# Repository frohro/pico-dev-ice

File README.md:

# <span style="text-transform: none;">The Pico Dev-iCE 📡</span>
**DSP Educational Vehicle & iCE40 Mixed-Signal Laboratory**

## 📌 Overview
The **Pico Dev-iCE** is a low-cost, high-performance "Lab-in-a-Box." It combines the high-speed programmable logic of a **Lattice iCE40UP5K FPGA** with the flexible C/MicroPython ecosystem of a **Raspberry Pi Pico (YD-RP2040 with 16MB Flash)**. 

Designed specifically as an educational platform, it abandons "black box" RF chips in favor of discrete, observable analog blocks. Students can physically probe the RF signal path, design their own LC filters on pluggable sandboxes, and write Verilog to perform Direct Digital Conversion (DDC), digital decimation, and hardware I2S audio routing.

Here is a video of the SDR receiving on 20 meters. 

The video has some drops in the audio that I don't detect unless I'm recording.

## 🚀 Key Capabilities
* **HF Software Defined Radio (RX/TX):** Full-duplex DDC/DUC transceiver covering 0 - 15.36 MHz (1st Nyquist) with Super-Nyquist capabilities up to 30+ MHz.
* **Vector Network Analyzer (VNA):** Built-in Return Loss Bridge (RLB) for S11 (reflection) antenna tuning, and Port-to-Port S21 (transmission) filter characterization.
* **Arbitrary Waveform Generator (AWG):** Dedicated DC-coupled and AC-coupled SMA outputs for 30 MSPS generic signal generation.
* **Real-Time Spectrum Analyzer:** Visualize the entire 15 MHz HF spectrum simultaneously via FPGA-accelerated FFTs.
* **Standalone Operation:** Onboard Audio DAC/Headphone amp and rotary encoder support allows the board to operate as a standalone radio without a PC.

#### Cost
I am not selling these, but the cost to order from JLCPCB for ten beards was about $700 plus taxes and shipping or for us in the US these days with tariffs and shipping it was about $1,100 for ten beards.  Version v0.1 works fine with the Raspberry Pi Pico or Pico W.  I recommend v0.15 which incorporates some resistors to quell EMI from the sharp edges of the iCE40UP5K.   You cannot turn the drive down on ouptups of this FPGA vi gateware.  The YD-RP20240 with its less optimum PCB layout must be modified to avoid occasional (71) USB errors.

---

## 🧠 Hardware Architecture

### Processing Core
* **Microcontroller:** YD-RP2040 / Pico 2 socket. Handles AGC math, user interface, USB communications, and slow-state hardware toggles. The massive internal Flash (up to 16MB) stores the FPGA bitstream and programs the FPGA directly on every boot, eliminating the need for an external FPGA flash chip.
* **FPGA:** Lattice iCE40UP5K (SG48). Handles high-speed 30.72 MHz DSP, NCO generation, CIC decimation/interpolation, and I2S master clocking.
* **Control Bus:** The Pico uses its high-speed `SPI0` bus to dual-role: it blasts the bitstream into the FPGA's internal CRAM on boot, and then seamlessly transitions to sending runtime DSP commands to the user's Verilog over the exact same 4 wires.

### Clocking & DSP Math
* **Master Clock:** A clean 30.720 MHz CMOS oscillator drives the FPGA.
* **The Magic of 30.72 MHz:** The FPGA decimates the 30.72 MSPS ADC data by exactly $R=640$ to yield a mathematically perfect **48.000 kHz** baseband I/Q audio stream over I2S to the Pico. 
* **Process Gain:** The 640x decimation provides ~ 28 dB of digital processing gain, turning the raw 8-bit ADC into a highly sensitive 12.6-bit effective receiver!

### The Receive (RX) Path
* **Topology:** `SMA` ➔ `Ethernet Isolation/CMC` ➔ `Band Sandbox` ➔ `T/R Switch` ➔ `LNA 1` ➔ `PGA (5/10dB)` ➔ `LNA 2` ➔ `ADC`.
* **Amplifiers:** Uses discrete high-speed op-amps wired as AC-coupled inverting amplifiers. 
* **Programmable Gain:** A Digital Step Attenuator (DSA) built from CMOS switches and precision T-networks, providing 0 to 55 dB of gain control in 5 dB steps. LNA 1 and LNA 2 are both bypassable to prevent clipping on massive signals.
* **ADC (MS9280):** 8-bit, 32 MSPS. Driven by an RF balun into True Differential Mode with a 4.5V analog supply, yielding a massive 4.0V peak-to-peak input span for maximum dynamic range.

### The Transmit (TX) Path
* **Topology:** `DAC` ➔ `Passive I-V` ➔ `Ethernet Transformer` ➔ `TX Switch` ➔ `Recon Sandbox` ➔ `TX Op-Amp (+12dB)` ➔ `T/R Switch` ➔ `SMA`.
* **DAC (MS9708):** 8-bit, 32 MSPS Current-Steering DAC.
* Passive 50Ω resistors and an Ethernet transformer gracefully map the DAC's strict output compliance limits into a clean 1.0V p-p RF signal, which is then amplified to drive a 50-ohm antenna.

### Power Domains (Strict Isolation)
To achieve commercial-grade noise floors, the noisy Switch-Mode Power Supply (SMPS) of standard Picos is bypassed/isolated. 
* **`+4.5V AVDD`:** Clean LDO powering the RF op-amps, analog switches, and ADC/DAC analog cores.
* **`+3.3V Digital`:** LDO powering the FPGA I/O, Pico, and IC logic.
* **`+3.3V Clean`:** Ferrite bead + LC filtered rail strictly for the 30.72 MHz oscillator to eliminate phase-noise/jitter.

---

## 🎛️ Port & Jumper Reference

### Coaxial Connectors
1. **`SDR_ANT`(BNC):** Main Transceiver Port (Transformer isolated, AC-Coupled).
2. **`SII` (SMA):** Device Under Test port for S11/VSWR Antenna measurements. Connects to the internal Return Loss Bridge.
3. **`AWG_OUT` (BNC):** Direct DC-coupled output (0V to +4V) from the DAC. Perfect for baseband signal generation.
4. **`S21` (SMA):** AC-coupled output for S21 Filter sweeps and RF signal generation. Protects the op-amp from DC-shorted filters.

### Filter Sandboxes (Plug-and-Play)
The board features `IN-GND-GND-OUT` 0.1" sockets for inserting custom filter daughterboards. 
* **Band Sandbox:** Shared by both RX and TX (pre-T/R switch). Students calculate and test bandpass filters here.
* **TX Pre-Sandbox:** Placed before the TX amplifier. Used for mild Nyquist reconstruction filters or super-Nyquist image-selection filters.

---

## 🛠️ Software & HDL Notes

* **Level Shifters (Logic Inversion):** The 4.5V analog switches are controlled by 3.3V GPIOs via 2N7002 N-Channel MOSFETs. **Note:** This results in a logic inversion. Writing `0` to the pin in MicroPython = Switch HIGH (Max Gain / Default Path). Writing `1` = Switch LOW (Attenuated / VNA / TX Path).
* **FPGA Boot & SPI0 Bus:** 
    *   The external FPGA Flash chip was removed to simplify the architecture. The Pico boots the FPGA directly by blasting the bitstream into CRAM using its Hardware `SPI0` block. 
    *   Because the Pico drives the bus, the net names match the Pico's hardware roles: `SPI0_TX` (MOSI) is data entering the FPGA, and `SPI0_RX` (MISO) is data leaving the FPGA. 
    *   **Runtime:** Once booted, the Pico reuses the exact same `SPI0` bus and `ICE_SSN` Chip Select pin to send DSP commands to the user's Verilog.
* **ADC OTR:** The MS9280 "Out of Range" (Clipping) pin pulses for only 32ns. The FPGA catches this, stretches the pulse, and triggers a hardware interrupt on the Pico to engage the AGC.

The ten-week, verification-first HDL course sequence is documented in
[`DDC_SDR_Lab_Plan.md`](DDC_SDR_Lab_Plan.md).

---

## 📍 Hardware Pinout Reference

### 1. Microcontroller (Raspberry Pi Pico) Pinout
*This map defines the interface for the software team handling AGC, VNA sweeps, user interface, and I2S audio routing.*

| Pico GPIO | Net Name | Function | Direction | Notes |
| :--- | :--- | :--- | :--- | :--- |
| **GPIO 0** | `FPGA_INT` | FPGA Hardware Interrupt | Input | Catches stretched ADC Out-Of-Range (OTR) pulses |
| **GPIO 1** | `PMOD_3` | PMOD / GPIO Jump | I/O | Connected via series resistor R32 to PMOD_3 |
| **GPIO 2** | `SDA` | I2C Data | In/Out | I2C bus for the OLED Display |
| **GPIO 3** | `SCL` | I2C Clock | Output | I2C bus for the OLED Display |
| **GPIO 4** | `SPI0_RX` | SPI0 MISO | Input | Data entering Pico from FPGA (via series resistor R33) |
| **GPIO 5** | `ICE_SSN` | SPI0 CSn (FPGA CS) | Output | Hardware SPI0 Chip Select (Boot & Runtime) |
| **GPIO 6** | `SPI0_CLK` | SPI0 SCK | Output | SPI Clock for Boot and Runtime (via series resistor R34) |
| **GPIO 7** | `SPI0_TX` | SPI0 MOSI | Output | Data leaving Pico to FPGA (via series resistor R35) |
| **GPIO 8** | `PGA0` | 5 dB Attenuator | Output | Logic 1 = Attenuator Active (LOW at switch) |
| **GPIO 9** | `PGA1` | 10 dB Attenuator | Output | Logic 1 = Attenuator Active (LOW at switch) |
| **GPIO 10** | `PGA2` | LNA 2 Bypass | Output | Logic 1 = LNA Bypassed (LOW at switch) |
| **GPIO 11** | `PGA3` | LNA 1 Bypass | Output | Logic 1 = LNA Bypassed (LOW at switch) |
| **GPIO 12** | `BAND_SW` | Band Filter Sandbox | Output | Toggles sandbox selection switch |
| **GPIO 13** | `TX_DATA` | I2S TX Data | Output | Full-Duplex Baseband Audio TO the FPGA |
| **GPIO 14** | `RX_DATA` | I2S RX Data | Input | Full-Duplex Baseband Audio FROM the FPGA |
| **GPIO 15** | `BCK` | I2S Bit Clock | Input | Clocks generated by FPGA (I2S Master) |
| **GPIO 16** | `WS` | I2S Word Select (L/R) | Input | Clocks generated by FPGA (I2S Master) |
| **GPIO 17** | `AF_DAC_DATA` | Audio DAC Data | Output | I2S out to standalone headphone amp |
| **GPIO 18** | `AF_DAC_MCLK` | Audio DAC Master | Output | I2S out to standalone headphone amp |
| **GPIO 19** | `AF_DAC_SCLK` | Audio DAC Clock | Output | I2S out to standalone headphone amp |
| **GPIO 20** | `AF_DAC_LRCK` | Audio DAC L/R | Output | I2S out to standalone headphone amp |
| **GPIO 21** | `ICE_DONE` | FPGA Boot Status | Input | Goes HIGH when FPGA is running and lights White LED |
| **GPIO 22** | `~ICE_RST` | FPGA Reset | Output | Pull LOW to hold FPGA in reset |
| **GPIO 26** | `REF` | Front-End RF Mux | Output | **0 = SDR RF Antenna RX**, 1 = VNA Input |
| **GPIO 27** | *(Optional)* | PMOD / GPIO Jump | I/O | Jumper JP3 maps to PMOD_2 |
| **GPIO 28** | `~T/R` | Transmit/Receive Sw | Output | **1 = RX Mode** (Antenna -> LNA), 0 = TX Mode |

### 2. FPGA (Lattice iCE40UP5K-SG48) Pinout
*This map defines the interface for the digital design team writing Verilog and the `.pcf` constraints file.*

| Pin # | Lattice Name | Net Name | Function / Connection |
| :---: | :--- | :--- | :--- |
| **37** | `IOT_45a_G1` | `CLK` | **30.72 MHz Master Clock IN** (From Oscillator) |
| **23** | `IOT_37a` | `ADC_CLK` | ADC Clock OUT (To MS9280 via 22Ω resistor) |
| **6** | `IOB_13b` | `DAC_CLK` | DAC Clock OUT (To MS9708) |
| **25** | `IOT_36b` | `D0` | ADC Data Bit 0 (LSB) |
| **26** | `IOT_39a` | `D1` | ADC Data Bit 1 |
| **27** | `IOT_38b` | `D2` | ADC Data Bit 2 |
| **28** | `IOT_41a` | `D3` | ADC Data Bit 3 |
| **31** | `IOT_42b` | `D4` | ADC Data Bit 4 |
| **32** | `IOT_43a` | `D5` | ADC Data Bit 5 |
| **34** | `IOT_44b` | `D6` | ADC Data Bit 6 |
| **35** | `IOT_46b_G0` | `D7` | ADC Data Bit 7 (MSB) |
| **36** | `IOT_48b` | `OTR` | ADC Out of Range (Clipping Flag) |
| **4** | `IOB_8a` | `DB0` | DAC Data Bit 0 (LSB) |
| **3** | `IOB_9b` | `DB1` | DAC Data Bit 1 |
| **2** | `IOB_6a` | `DB2` | DAC Data Bit 2 |
| **48** | `IOB_4a` | `DB3` | DAC Data Bit 3 |
| **47** | `IOB_2a` | `DB4` | DAC Data Bit 4 |
| **46** | `IOB_0a` | `DB5` | DAC Data Bit 5 |
| **45** | `IOB_5b` | `DB6` | DAC Data Bit 6 |
| **44** | `IOB_3b_G6` | `DB7` | DAC Data Bit 7 (MSB) |
| **14** | `IOB_32a_SPI_SO` | `SPI0_RX` | SPI MISO (Data *to* Pico during runtime) |
| **17** | `IOB_33b_SPI_SI` | `SPI0_TX` | SPI MOSI (Data *from* Pico during runtime) |
| **15** | `IOB_34a_SPI_SCK`| `SPI0_CLK` | SPI Clock IN (From Pico GPIO 6) |
| **16** | `IOB_35b_SPI_SS` | `ICE_SSN` | SPI Chip Select IN (From Pico GPIO 5) |
| **12** | `IOB_22a` | `BCK` | I2S Bit Clock OUT (To Pico GPIO 15) |
| **9** | `IOB_16a` | `WS` | I2S Word Select OUT (To Pico GPIO 16) |
| **11** | `IOB_20a` | `RX_DATA` | I2S Data OUT (SDR audio to Pico GPIO 14) |
| **10** | `IOB_18a` | `TX_DATA` | I2S Data IN (Transmit audio from Pico GPIO 13) |
| **13** | `IOB_24a` | `FPGA_INT` | Hardware Interrupt OUT (To Pico GPIO 0) |
| **38** | `IOT_50b` | `ANG_0` | Rotary Encoder / Tuning Knob A |
| **42** | `IOT_51a` | `ANG_1` | Rotary Encoder / Tuning Knob B |
| **43** | `IOT_49a` | `ANG_2` | Rotary Encoder / Tuning Knob Switch |
| **21** | `IOB_23b` | `PMOD_0` | PMOD Header Pin 1 |
| **19** | `IOB_29b` | `PMOD_1` | PMOD Header Pin 2 |
| **18** | `IOB_31b` | `PMOD_2` | PMOD Header Pin 3 |
| **20** | `IOB_25b_G3` | `PMOD_3` | PMOD Header Pin 4 |
| **39** | `RGB0` | `RED` | Open-Drain LED Driver (Active-Low: 0=ON, pulses on ADC OTR clipping) |
| **40** | `RGB1` | `YELLOW` | Open-Drain LED Driver (Active-Low: 0=ON, pulses on SPI tuning activity) |
| **41** | `RGB2` | `GREEN` | Open-Drain LED Driver (Active-Low: 0=ON, steady ON when un-reset) |
| **7** | `CDONE` | `ICE_DONE` | *Hardware Boot / Status Out* |
| **8** | `~CRESET` | `~ICE_RST` | *Hardware Boot / Reset In* |

## Pico SDK Bring-Up

The SDK port is under `Software/pico-ice-sdk`. It uses the checked-in Pico SDK
(currently 2.2.0). The general SDK examples use the TinyUSB revision bundled by
that SDK. The DDC firmware below uses a newer TinyUSB checkout because it needs
the UAC1 descriptor definitions that are not present in the bundled revision.

The smallest board-specific firmware example programs the FPGA's volatile CRAM directly from the RP2040:

```sh
cmake -S Software/pico-ice-sdk/examples/rp2_dev_ice_blinky \
    -B Software/pico-ice-sdk/examples/rp2_dev_ice_blinky/build \
    -DPICO_BOARD=pico_dev_ice -DPICO_NO_PICOTOOL=1
cmake --build Software/pico-ice-sdk/examples/rp2_dev_ice_blinky/build
```

The generated UF2 is RP2040 firmware that contains the FPGA bitstream. The Dev-iCE has no external FPGA configuration flash, so the board port excludes the external-flash and TinyUF2 FPGA-storage paths. SPI0 GPIO 6 is the CRAM transfer clock and GPIO 7 carries configuration data; normal FPGA operation uses the separate external 30.720 MHz oscillator, not a Pico-generated clock on GPIO 27.

## DDC SDR Firmware

The first Dev-iCE SDR application is in
[`Software/ddc_sdr_firmware`](Software/ddc_sdr_firmware). It replaces the
earlier Si5351a, Tayloe detector, and PCM1808 path with FPGA-generated DDC I/Q data received as
PCM1808-compatible I2S. The Pico firmware:

* programs the FPGA's volatile CRAM over SPI0;
* reuses SPI0 for runtime frequency and sample-rate commands;
* captures FPGA I2S with DMA; and
* exposes stereo 24-bit UAC1 audio at 48 kHz and 96 kHz, CDC control, and a
    DFU interface.

The DDC application requires a TinyUSB checkout with both `src/tusb.h` and
`hw/bsp/rp2040`. A current checkout at `$HOME/tinyusb` is detected
automatically, or it can be selected explicitly:

```sh
cmake -S Software/ddc_sdr_firmware -B Software/ddc_sdr_firmware/build \
        -DPICO_TINYUSB_PATH="$HOME/tinyusb" \
        -DPICO_BOARD=pico_dev_ice \
        -DPICO_NO_PICOTOOL=1
cmake --build Software/ddc_sdr_firmware/build -j2
```

The Pico firmware keeps FPGA deployment easy to choose: `FPGA_BOOT_MODE=DFU`
waits for a development bitstream from `dfu-util`, while
`FPGA_BOOT_MODE=STORED` loads an image embedded in the Pico firmware at boot.
Two stored transceiver profiles can be included with
`FPGA_RX_BITSTREAM_BIN` and `FPGA_TX_BITSTREAM_BIN`, with
`FPGA_DEFAULT_IMAGE` selecting the boot profile and `FPGA,LOAD,RX` or
`FPGA,LOAD,TX` selecting one between sessions. The full commands and build
examples are in [`Software/ddc_sdr_firmware/README.md`](Software/ddc_sdr_firmware/README.md).

These profile loads are not a VNA sweep mechanism. A VNA needs a single
coherent FPGA design containing the stimulus, reference, receive, and
measurement paths for the complete sweep. Select a persistent VNA-capable
image before a measurement, or implement those paths in one integrated image;
do not reconfigure between sweep points.

For development, compile an FPGA bitstream with Yosys, nextpnr-ice40, and
icepack, then load it without reflashing the Pico:

```sh
python3 Software/ddc_sdr_firmware/tools/dfu_fpga.py /path/to/ddc_sdr.bin
```

Stop the SDR++ or Quisk audio stream before starting DFU. The helper prepares
the shared SPI0 bus, sends the packed bitstream through `dfu-util`, and lets the
Pico restore the runtime FPGA state afterward. Do not reset the Pico after a
DFU-only update: FPGA CRAM is volatile and a reset clears the loaded design.

For the complete pinout, SPI protocol, CDC commands, build options, and DFU
sequence, see [`Software/ddc_sdr_firmware/README.md`](Software/ddc_sdr_firmware/README.md).

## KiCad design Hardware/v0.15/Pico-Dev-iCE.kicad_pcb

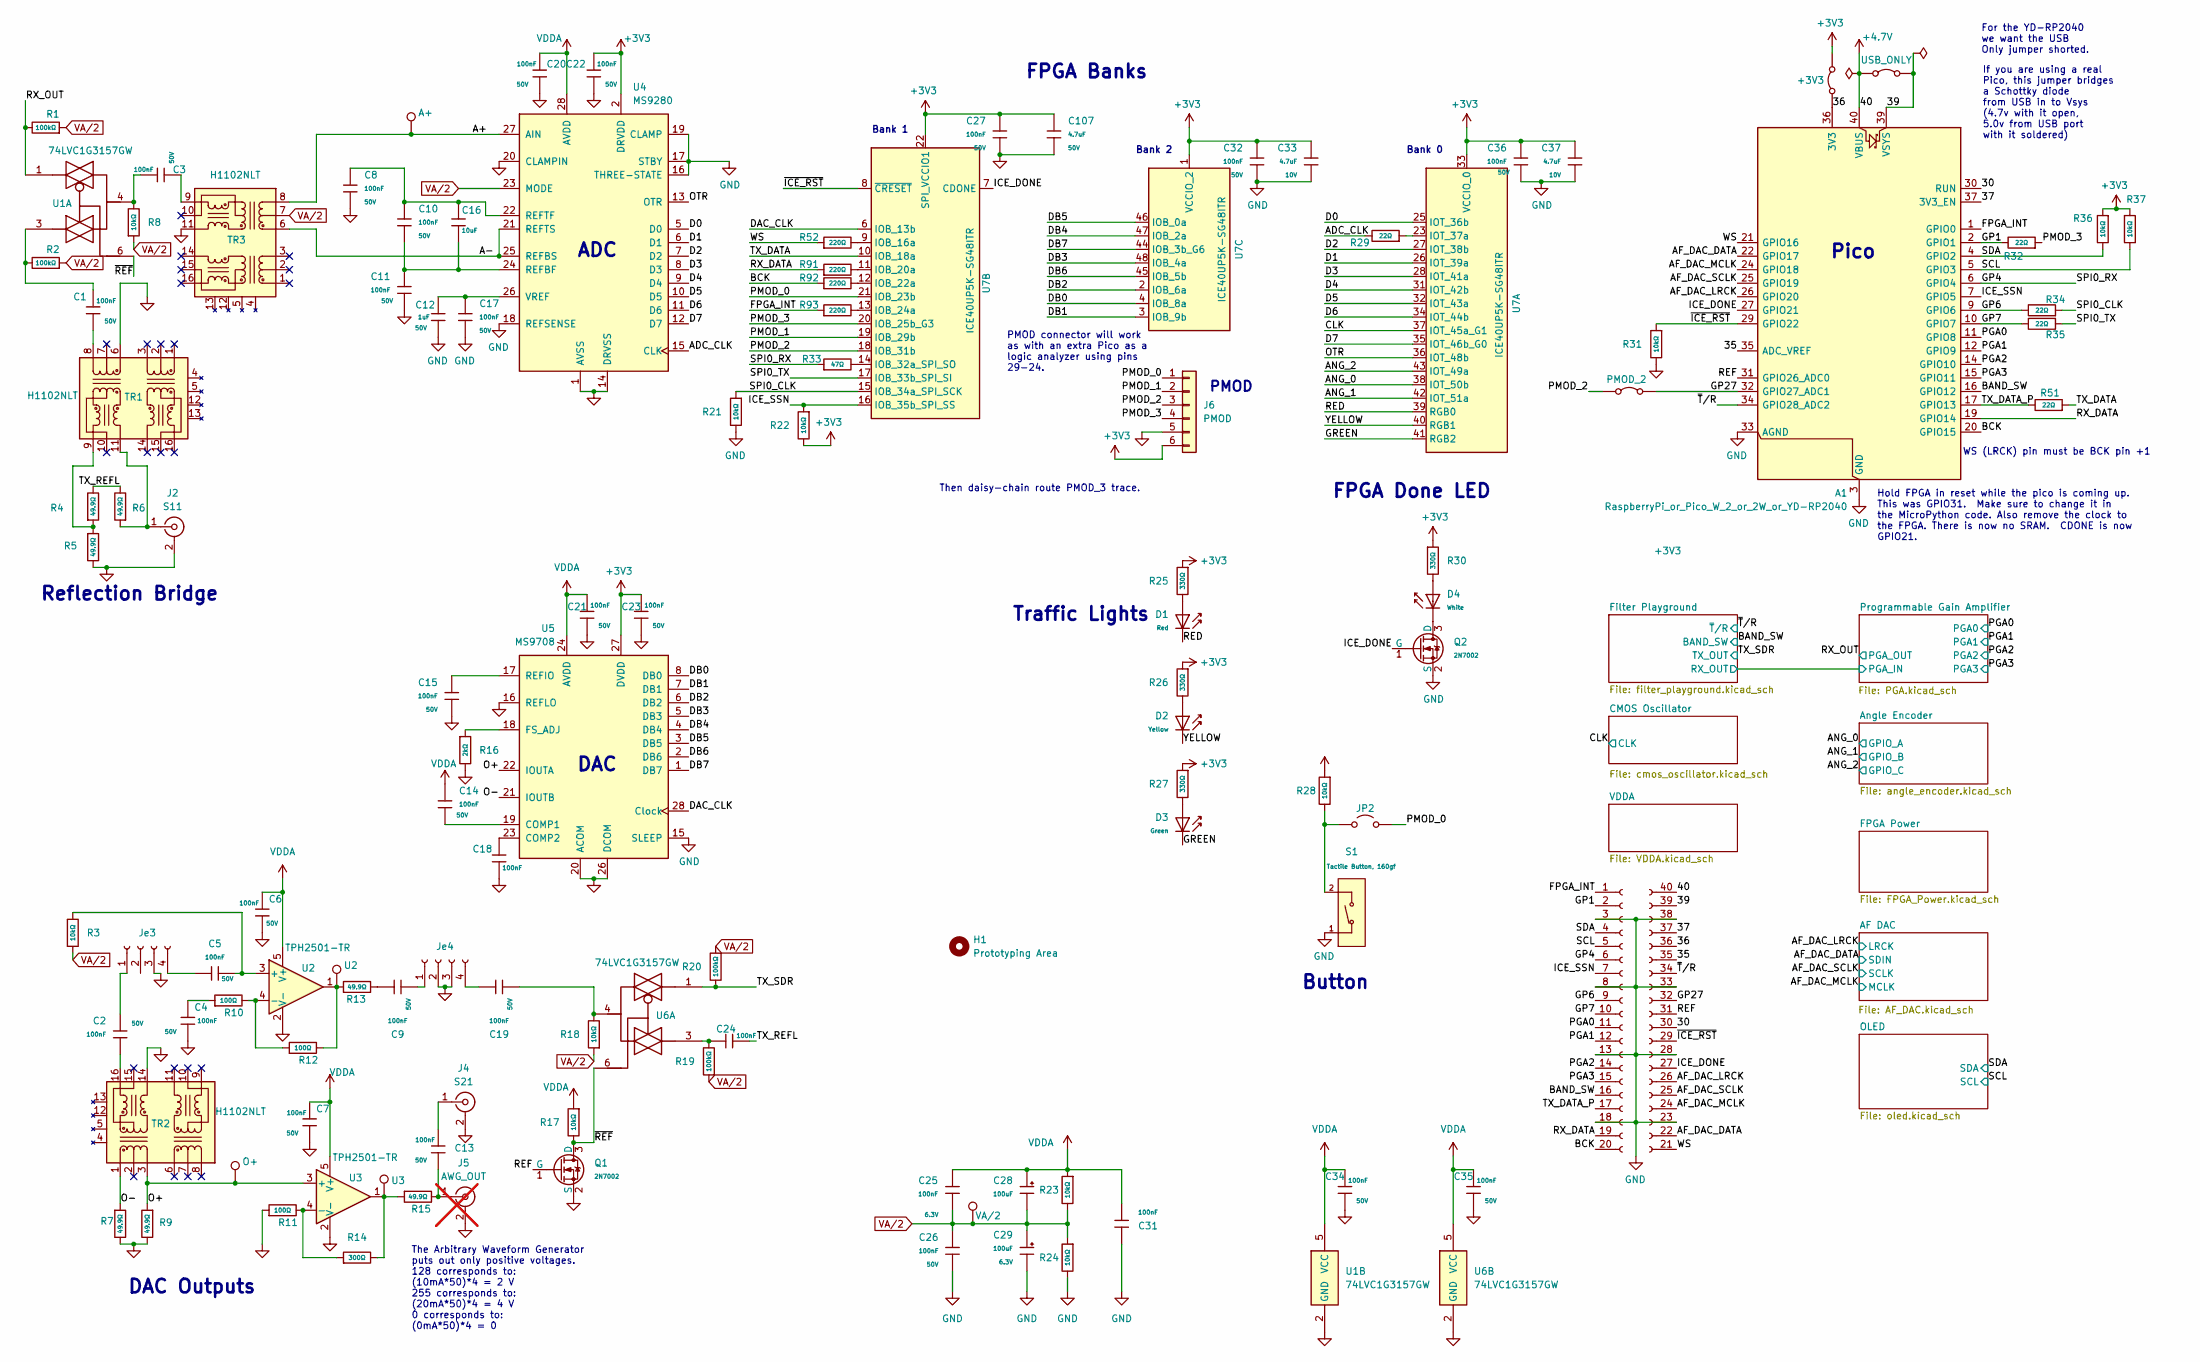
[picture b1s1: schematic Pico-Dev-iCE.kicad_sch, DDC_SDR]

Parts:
A1: RaspberryPi_or_Pico_W_2_or_2W_or_YD-RP2040; RaspberryPi_Pico_Common_THT
C1, C2, C3, C4, C5, C6, C7, C8, C9, C10, C11, C13, C14, C15, C17, C18, C19, C20, C21, C22, C23, C24, C25, C26, C27, C31, C32, C34, C35, C36: 100nF; C_0402; Voltage Rated 50V; Tolerance ±10%; Part CL05B104KB54PNC; LCSC C307331
C12: 1uF; C_0603; Voltage Rated 50V; Tolerance ±10%; Part CL10A105KB8NNNC; LCSC C15849
C16: 10uF; C_0805; Voltage Rated 50V; Tolerance ±10%; Part GRM21BR61H106KE43L; LCSC C440198
C28, C29: 100uF; C_CASE-B-3528-21(mm); Tolerance ±10%; Rated Voltage 6.3V; Part TAJB107K006RNJ; LCSC C16133
C33, C37: 4.7uF; C_0402; Voltage Rated 10V; Tolerance ±20%; Part CL05A475MP5NRNC; LCSC C23733
C107: 4.7uF; C_1206; Voltage Rated 50V; Tolerance ±10%; Part 1206B475K500NT; LCSC C29823
D1: Red; D_0805; Forward Voltage (VF) 1.6V~2.6V; Part NCD0805R1; LCSC C84256
D2: Yellow; D_0805; Part KT-0805Y; LCSC C2296
D3: Green; D_0805; Part KT-0805G; LCSC C2297
D4: White; D_0805; Part KT-0805W; LCSC C34499
H1: Prototyping Area; Prototype_array
J2: S11; SMA_Samtec_SMA-J-P-H-ST-EM1_EdgeMount; LCSC C52766461
J4: S21; SMA_Samtec_SMA-J-P-H-ST-EM1_EdgeMount; LCSC C52766461
J5: AWG_OUT; Conn_Coaxial_Frohne; not fitted
J6: PMOD; PinSocket_1x06_P2.54mm_Vertical; LCSC C52148815
J11: Conn_01x20_Socket; PinSocket_1x20_P2.54mm_Vertical; LCSC C2905423
J12: Conn_01x20_Socket; PinSocket_1x20_P2.54mm_Vertical-pins21-40; LCSC C2905423
JP2: Jumper_2_Open; SolderJumper-2_P1.3mm_Open_RoundedPad1.0x1.5mm
JP3: PMOD_2; SolderJumper-2_P1.3mm_Bridged2Bar_RoundedPad1.0x1.5mm
JP4: USB_ONLY; SolderJumper-2_P1.3mm_Bridged2Bar_RoundedPad1.0x1.5mm
JP8: +3V3; SolderJumper-2_P1.3mm_Bridged2Bar_RoundedPad1.0x1.5mm
Je3, Je4: Filter; PinHeader_1x04_P2.54mm_Vertical; LCSC C2718488
Q1, Q2: 2N7002; Q_SOT-23; Part 2N7002K; LCSC C22379475
R1, R2, R19, R20: 100kΩ; R_0402; Overload Voltage (Max) 50V; Tolerance ±1%; Part 0402WGF1003TCE; LCSC C25741
R3, R8, R17, R18, R21, R22, R23, R24, R28, R31, R36, R37: 10kΩ; R_0402; Overload Voltage (Max) 50V; Tolerance ±1%; Part 0402WGF1002TCE; LCSC C25744
R4, R5, R6, R7, R9, R13, R15: 49.9Ω; R_0402; Overload Voltage (Max) 50V; Tolerance ±1%; Part 0402WGF499JTCE; LCSC C25120
R10, R11, R12: 100Ω; R_0805; Overload Voltage (Max) 150V; Tolerance ±1%; Part 0805W8F1000T5E; LCSC C17408
R14: 300Ω; R_0805; Overload Voltage (Max) 150V; Tolerance ±1%; Part 0805W8F3000T5E; LCSC C17617
R16: 2kΩ; R_0402; Overload Voltage (Max) 50V; Tolerance ±1%; Part 0402WGF2001TCE; LCSC C4109
R25, R26, R27, R30: 330Ω; R_0402; Overload Voltage (Max) 50V; Tolerance ±1%; Part 0402WGF3300TCE; LCSC C25104
R29, R32, R34, R35, R51: 22Ω; R_0402; Overload Voltage (Max) 50V; Tolerance ±1%; Part 0402WGF220JTCE; LCSC C25092
R33: 47Ω; R_0402; Overload Voltage (Max) 50V; Tolerance ±1%; Part 0402WGF470JTCE; LCSC C25118
R52, R91, R92, R93: 220Ω; R_0402; Overload Voltage (Max) 50V; Tolerance ±1%; Part 0402WGF2200TCE; LCSC C25091
S1: Tactile Button, 160gf; SW_TS-1088-AR02016; Voltage Rating (Dc) 12V; Part TS-1088-AR02016; LCSC C720477
TP1: U2; TestPoint_THTPad_D2.5mm_Drill1.2mm
TP2: U3; TestPoint_THTPad_D2.5mm_Drill1.2mm
TP3: VA/2; TestPoint_THTPad_D2.5mm_Drill1.2mm
TP14: O+; TestPoint_THTPad_D2.5mm_Drill1.2mm
TP15: A+; TestPoint_THTPad_D2.5mm_Drill1.2mm
TR1, TR2, TR3: H1102NLT; Transformer_Ethernet_Wuerth_749013011A; LCSC C20623173
U1, U6: 74LVC1G3157GW; SOT-363_SC-70-6; LCSC C52140494
U2, U3: TPH2501-TR; SOT-23-5; LCSC C126713
U4: MS9280; SSOP-28_5.3x10.2mm_P0.65mm; LCSC C1509021
U5: MS9708; TSSOP-28-1EP_4.4x9.7mm_P0.65mm_EP3.4x9.7mm_Mask3.1x4.05mm_T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; LCSC C1509022
U7: ICE40UP5K-SG48ITR; QFN-48-1EP_7x7mm_P0.5mm_EP5.6x5.6mm; MPN ICE40UP5K-SG48I; LCSC C2678152

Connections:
+3V3: C22.1, C23.1, C27.1, C32.1, C33.1, C36.1, C37.1, C107.1, J6.6, JP8.2 (B), R22.2, R25.1, R26.1, R27.1, R28.1, R30.1, R36.1, R37.1, U4.2 (DRVDD), U5.27 (DVDD), U7.1 (VCCIO_2), U7.22 (SPI_VCCIO1), U7.33 (VCCIO_0); also elsewhere on the board
+4.7V: A1.40 (VBUS), J12.40 (Pin_1), JP4.1 (A); also elsewhere on the board
/30: A1.30 (RUN), J12.30 (Pin_11)
/35: A1.35 (ADC_VREF), J12.35 (Pin_6)
/36: A1.36 (3V3), J12.36 (Pin_5), JP8.1 (A)
/37: A1.37 (3V3_EN), J12.37 (Pin_4)
/39: A1.39 (VSYS), J12.39 (Pin_2), JP4.2 (B)
/A+: TP15.1 (1_1), TR3.8 (RD-), U4.27 (AIN)
/A-: TR3.6 (RD+), U4.21 (REFTS), U4.25 (REFBS)
/ADC_CLK: R29.2, U4.15 (CLK)
/AF_DAC_DATA: A1.22 (GPIO17), J12.22 (Pin_19); also elsewhere on the board
/AF_DAC_LRCK: A1.26 (GPIO20), J12.26 (Pin_15); also elsewhere on the board
/AF_DAC_MCLK: A1.24 (GPIO18), J12.24 (Pin_17); also elsewhere on the board
/AF_DAC_SCLK: A1.25 (GPIO19), J12.25 (Pin_16); also elsewhere on the board
/ANG_0: U7.38 (IOT_50b); also elsewhere on the board
/ANG_1: U7.42 (IOT_51a); also elsewhere on the board
/ANG_2: U7.43 (IOT_49a); also elsewhere on the board
/BAND_SW: A1.16 (GPIO12), J11.16; also elsewhere on the board
/BCK: A1.20 (GPIO15), J11.20, R92.1
/CLK: U7.37 (IOT_45a_G1); also elsewhere on the board
/D0: U4.5 (D0), U7.25 (IOT_36b)
/D1: U4.6 (D1), U7.26 (IOT_39a)
/D2: U4.7 (D2), U7.27 (IOT_38b)
/D3: U4.8 (D3), U7.28 (IOT_41a)
/D4: U4.9 (D4), U7.31 (IOT_42b)
/D5: U4.10 (D5), U7.32 (IOT_43a)
/D6: U4.11 (D6), U7.34 (IOT_44b)
/D7: U4.12 (D7), U7.35 (IOT_46b_G0)
/DAC_CLK: U5.28 (Clock), U7.6 (IOB_13b)
/DB0: U5.8 (DB0), U7.4 (IOB_8a)
/DB1: U5.7 (DB1), U7.3 (IOB_9b)
/DB2: U5.6 (DB2), U7.2 (IOB_6a)
/DB3: U5.5 (DB3), U7.48 (IOB_4a)
/DB4: U5.4 (DB4), U7.47 (IOB_2a)
/DB5: U5.3 (DB5), U7.46 (IOB_0a)
/DB6: U5.2 (DB6), U7.45 (IOB_5b)
/DB7: U5.1 (DB7), U7.44 (IOB_3b_G6)
/FPGA_INT: A1.1 (GPIO0), J11.1, R93.1
/GP1: A1.2 (GPIO1), J11.2, R32.2
/GP4: A1.6 (GPIO4), J11.6, R33.1
/GP6: A1.9 (GPIO6), J11.9, R34.2
/GP7: A1.10 (GPIO7), J11.10, R35.2
/GP27: A1.32 (GPIO27_ADC1), J12.32 (Pin_9), JP3.2 (B)
/GREEN: D3.1, U7.41 (RGB2)
/ICE_DONE: A1.27 (GPIO21), J12.27 (Pin_14), Q2.1 (G), U7.7 (CDONE)
/ICE_SSN: A1.7 (GPIO5), J11.7, R22.1, U7.16 (IOB_35b_SPI_SS)
/O+: R9.1, TP14.1 (1_1), TR2.3 (TD-), U3.3 (+), U5.22 (IOUTA)
/O-: R7.1, TR2.1 (TD+), U5.21 (IOUTB)
/OTR: U4.13 (OTR), U7.36 (IOT_48b)
/PGA0: A1.11 (GPIO8), J11.11; also elsewhere on the board
/PGA1: A1.12 (GPIO9), J11.12; also elsewhere on the board
/PGA2: A1.14 (GPIO10), J11.14; also elsewhere on the board
/PGA3: A1.15 (GPIO11), J11.15; also elsewhere on the board
/PMOD_0: J6.1, JP2.1 (A), U7.21 (IOB_23b)
/PMOD_1: J6.2, U7.19 (IOB_29b)
/PMOD_2: J6.3, JP3.1 (A), U7.18 (IOB_31b)
/PMOD_3: J6.4, R32.1, U7.20 (IOB_25b_G3)
/RED: D1.1, U7.39 (RGB0)
/REF: A1.31 (GPIO26_ADC0), J12.31 (Pin_10), Q1.1 (G)
/RX_DATA: A1.19 (GPIO14), J11.19, R91.1
/RX_OUT: R1.2, U1.1; also elsewhere on the board
/SCL: A1.5 (GPIO3), J11.5, R37.2; also elsewhere on the board
/SDA: A1.4 (GPIO2), J11.4, R36.2; also elsewhere on the board
/SPI0_CLK: R21.1, R34.1, U7.15 (IOB_34a_SPI_SCK)
/SPI0_TX: R35.1, U7.17 (IOB_33b_SPI_SI)
/TX_DATA: R51.1, U7.10 (IOB_18a)
/TX_DATA_P: A1.17 (GPIO13), J11.17, R51.2
/TX_REFL: C24.1, R4.2, R6.2
/TX_SDR: R20.2, U6.1; also elsewhere on the board
/WS: A1.21 (GPIO16), J12.21 (Pin_20), R52.1
/YELLOW: D2.1, U7.40 (RGB1)
/~ICE_RST: A1.29 (GPIO22), J12.29 (Pin_12), R31.1, U7.8 (~CRESET)
/~REF: Q1.3 (D), R17.2, U1.6, U6.6
/~T/R: A1.34 (GPIO28_ADC2), J12.34 (Pin_7); also elsewhere on the board
GND: A1.3 (GND), A1.8 (GND), A1.13 (GND), A1.18 (GND), A1.23 (GND), A1.28 (GND), A1.33 (AGND), A1.38 (GND), C4.2, C6.2, C7.2, C8.2, C11.2, C12.2, C15.2, C17.2, C18.2, C20.2, C21.2, C22.2, C23.2, C26.1, C27.2, C29.2, C31.1, C32.2, C33.2, C34.2, C35.2, C36.2, C37.2, C107.2, J2.2 (Ext), J4.2 (Ext), J5.2 (Ext), J6.5, J11.3, J11.8, J11.13, J11.18, J12.23 (Pin_18), J12.28 (Pin_13), J12.33 (Pin_8), J12.38 (Pin_3), Je3.3, Je4.2, Je4.3, Q1.2 (S), Q2.2 (S), R5.2, R7.2, R9.2, R11.1, R16.2, R21.2, R24.2, R31.2, S1.1 (A), TR1.6 (RD+), TR2.14 (TX-), TR3.11 (RX+), U1.2 (GND), U2.2 (V-), U3.2 (V-), U4.1 (AVSS), U4.14 (DRVSS), U4.16 (THREE-STATE), U4.17 (STBY), U4.18 (REFSENSE), U4.19 (CLAMP), U4.20 (CLAMPIN), U5.15 (SLEEP), U5.16 (REFLO), U5.20 (ACOM), U5.26 (DCOM), U6.2 (GND); also elsewhere on the board
unnamed: C1.1, R2.2, U1.3
unnamed: C3.1, R8.2, U1.4
unnamed: C4.1, R10.1
unnamed: C9.1, R13.2
unnamed: C19.2, R18.2, U6.4
unnamed: C24.2, R19.2, U6.3
unnamed: D1.2, R25.2
unnamed: D2.2, R26.2
unnamed: D3.2, R27.2
unnamed: D4.2, R30.2
unnamed: J2.1 (In), R6.1, TR1.11 (RX+)
unnamed: C13.1, J4.1 (In)
unnamed: C13.2, J5.1 (In), R15.2
unnamed: JP2.2 (B), R28.2, S1.2 (B)
unnamed: C2.2, Je3.1
unnamed: C5.1, Je3.4
unnamed: C9.2, Je4.1
unnamed: C19.1, Je4.4
unnamed: D4.1, Q2.3 (D)
unnamed: R12.2, R13.1, TP1.1 (1_1), U2.1
unnamed: R14.2, R15.1, TP2.1 (1_1), U3.1
unnamed: C1.2, TR1.8 (RD-)
unnamed: R4.1, R5.1, TR1.9 (RX-)
unnamed: C2.1, TR2.16 (TX+)
unnamed: C3.2, TR3.9 (RX-)
unnamed: C5.2, R3.2, U2.3 (+)
unnamed: R10.2, R12.1, U2.4 (-)
unnamed: R11.2, R14.1, U3.4 (-)
unnamed: C10.2, C11.1, C16.2, U4.24 (REFBF)
unnamed: C8.1, C10.1, C16.1, U4.22 (REFTF)
unnamed: C12.1, C17.1, U4.26 (VREF)
unnamed: C14.2, U5.19 (COMP1)
unnamed: C18.1, U5.23 (COMP2)
unnamed: R16.1, U5.18 (FS_ADJ)
unnamed: C15.1, U5.17 (REFIO)
unnamed: R29.1, U7.23 (IOT_37a)
unnamed: R52.2, U7.9 (IOB_16a)
unnamed: R91.2, U7.11 (IOB_20a)
unnamed: R92.2, U7.12 (IOB_22a)
unnamed: R93.2, U7.13 (IOB_24a)
unnamed: R33.2, U7.14 (IOB_32a_SPI_SO)
VA/2: C25.1, C26.2, C28.2, C29.1, R1.1, R2.1, R3.1, R8.1, R18.1, R19.1, R20.1, R23.2, R24.1, TP3.1 (1_1), TR3.7 (C_RD), U4.23 (MODE); also elsewhere on the board
VDDA: C6.1, C7.1, C14.1, C20.1, C21.1, C25.2, C28.1, C31.2, C34.1, C35.1, R17.1, R23.1, U1.5 (VCC), U2.5 (V+), U3.5 (V+), U4.28 (AVDD), U5.24 (AVDD), U6.5 (VCC); also elsewhere on the board

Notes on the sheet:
FPGA Done LED
Pico
Traffic Lights
Then daisy-chain route PMOD_3 trace.
Bank 1
Bank 0
Hold FPGA in reset while the pico is coming up. This was GPIO31. Make sure to change it in the MicroPython code. Also remove the clock to the FPGA. There is now no SRAM. CDONE is now GPIO21.
WS (LRCK) pin must be BCK pin +1
PMOD
FPGA Banks
If you are using a real Pico, this jumper bridges a Schottky diode from USB in to Vsys (4.7v with it open, 5.0v from USB port with it soldered)
DAC Outputs
Bank 2
The Arbitrary Waveform Generator puts out only positive voltages. 128 corresponds to: (10mA*50)*4 = 2 V 255 corresponds to: (20mA*50)*4 = 4 V 0 corresponds to: (0mA*50)*4 = 0
For the YD-RP2040 we want the USB Only jumper shorted.
DAC
Reflection Bridge
Button
PMOD connector will work as with an extra Pico as a logic analyzer using pins 29-24.
ADC

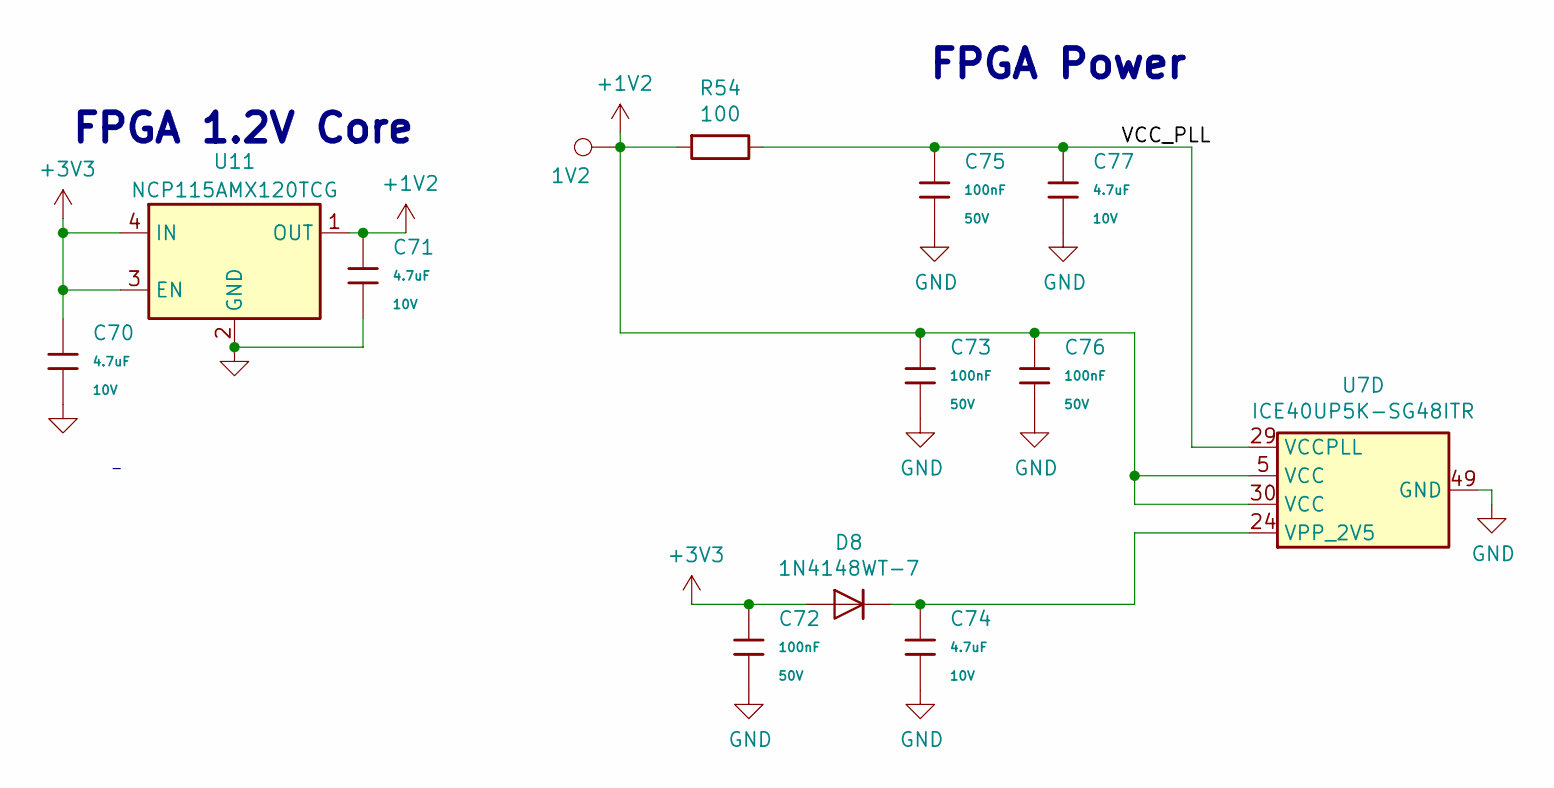
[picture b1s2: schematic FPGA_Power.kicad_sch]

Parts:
C70, C71, C74, C77: 4.7uF; C_0402; Voltage Rated 10V; Tolerance ±20%; Part CL05A475MP5NRNC; LCSC C23733
C72, C73, C75, C76: 100nF; C_0402; Voltage Rated 50V; Tolerance ±10%; Part CL05B104KB54PNC; LCSC C307331
D8: 1N4148WT-7; D_SOD-523; MPN 1N4148WT-7; LCSC C27748
R54: 100; R_0402_1005Metric; MPN RC0402FR-07100RL; LCSC C25076
TP9: 1V2; TestPoint_THTPad_D2.5mm_Drill1.2mm
U7: ICE40UP5K-SG48ITR; QFN-48-1EP_7x7mm_P0.5mm_EP5.6x5.6mm; MPN ICE40UP5K-SG48I; LCSC C2678152
U11: NCP115AMX120TCG; OnSemi_XDFN4-1EP_1.0x1.0mm_EP0.52x0.52mm; MPN NCP115AMX120TCG; LCSC C603500

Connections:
+1V2: C71.1, C73.1, C76.1, R54.2, TP9.1 (1_1), U7.5 (VCC), U7.30 (VCC), U11.1 (OUT)
+3V3: C70.1, C72.1, D8.2 (A), U11.3 (EN), U11.4 (IN); also elsewhere on the board
/FPGA Power/VCC_PLL: C75.1, C77.1, R54.1, U7.29 (VCCPLL)
GND: C70.2, C71.2, C72.2, C73.2, C74.2, C75.2, C76.2, C77.2, U7.49 (GND), U11.2 (GND), U11.5 (GND); also elsewhere on the board
unnamed: C74.1, D8.1 (K), U7.24 (VPP_2V5)

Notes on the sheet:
FPGA Power
FPGA 1.2V Core

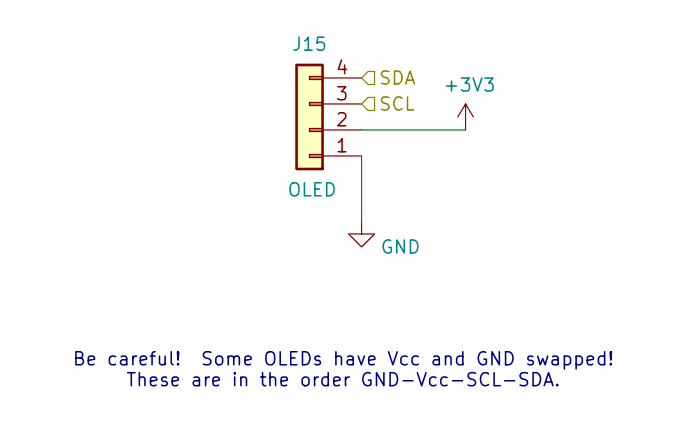
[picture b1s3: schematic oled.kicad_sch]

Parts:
J15: OLED; PinSocket_1x04_P2.54mm_Vertical; LCSC C2718488

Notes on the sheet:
Be careful! Some OLEDs have Vcc and GND swapped! These are in the order GND-Vcc-SCL-SDA.

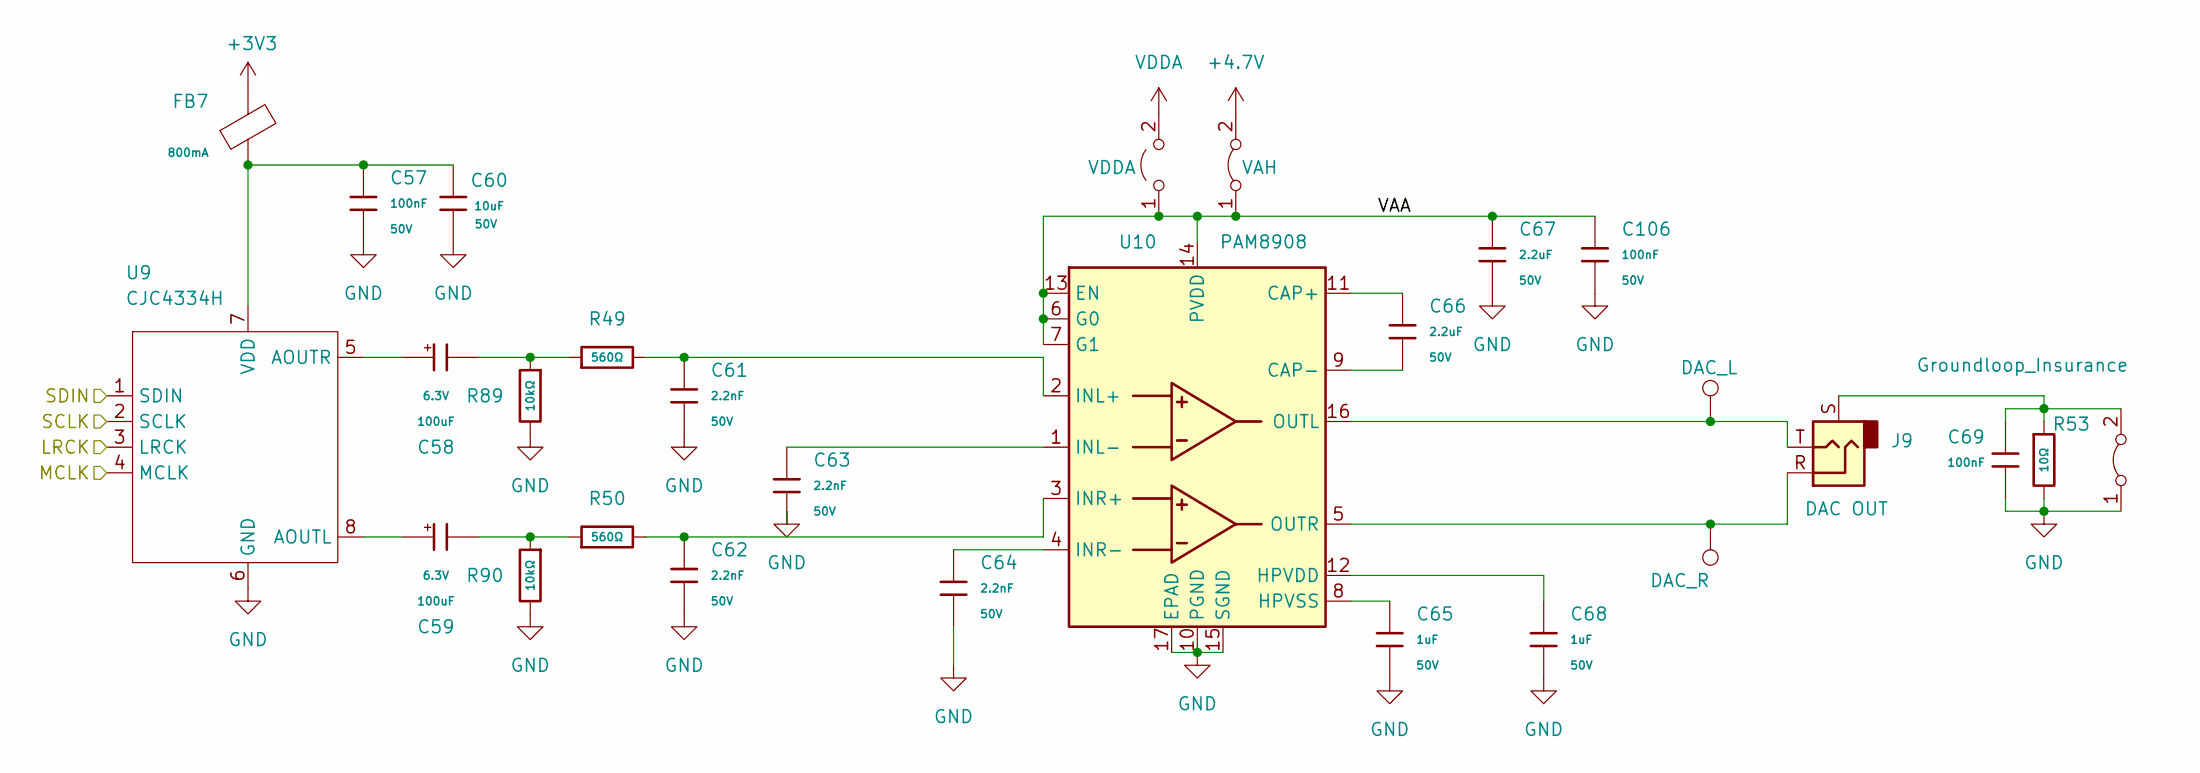
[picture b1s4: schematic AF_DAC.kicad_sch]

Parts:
C57, C69, C106: 100nF; C_0402; Voltage Rated 50V; Tolerance ±10%; Part CL05B104KB54PNC; LCSC C307331
C58, C59: 100uF; C_CASE-B-3528-21(mm); Tolerance ±10%; Rated Voltage 6.3V; Part TAJB107K006RNJ; LCSC C16133
C60: 10uF; C_0805; Tolerance ±10%; Rated Voltage 16V; Part GRM21BR61H106KE43L; LCSC C440198
C61, C62, C63, C64: 2.2nF; C_0805; Voltage Rated 50V; Tolerance ±5%; Part CL21C222JBFNNNE; LCSC C28260
C65, C68: 1uF; C_0603; Voltage Rated 50V; Tolerance ±10%; Part CL10A105KB8NNNC; LCSC C15849
C66, C67: 2.2uF; C_0805; Voltage Rated 50V; Tolerance ±10%; Part CL21A225KBQNNNE; LCSC C377773
FB7: FB_0805; Current Rating 800mA; Tolerance ±25%; Part GZ2012D101TF; LCSC C1015
J9: 3.5mm_Jack; Jack_3.5mm_CUI_SJ-3523-SMT_Horizontal; LCSC C18594
JP6: VDDA; SolderJumper-2_P1.3mm_Open_RoundedPad1.0x1.5mm
R49, R50: 560Ω; R_0603; Overload Voltage (Max) 75V; Tolerance ±1%; Part 0603WAF5600T5E; LCSC C23204
R53: 10Ω; R_0603; Overload Voltage (Max) 75V; Tolerance ±1%; Part 0603WAF100JT5E; LCSC C22859
R89, R90: 10kΩ; R_0402; Overload Voltage (Max) 50V; Tolerance ±1%; Part 0402WGF1002TCE; LCSC C25744
TP7: DAC_L; TestPoint_THTPad_D2.5mm_Drill1.2mm
TP8: DAC_R; TestPoint_THTPad_D2.5mm_Drill1.2mm
U9: CJC4334H; SOIC-8_3.9x4.9mm_P1.27mm; LCSC C41417670
U10: PAM8908; QFN-16-1EP_3x3mm_P0.5mm_EP1.7x1.7mm; LCSC C33233
e3: VAH; SolderJumper-2_P1.3mm_Bridged_RoundedPad1.0x1.5mm
e4: Groundloop_Insurance; SolderJumper-2_P1.3mm_Bridged_RoundedPad1.0x1.5mm

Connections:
+3V3: FB7.2; also elsewhere on the board
+4.7V: e3.2 (B); also elsewhere on the board
/AF DAC/VAA: C67.1, C106.1, JP6.1 (A), U10.6 (G0), U10.7 (G1), U10.13 (EN), U10.14 (PVDD), e3.1 (A)
/AF_DAC_DATA: U9.1 (SDIN); also elsewhere on the board
/AF_DAC_LRCK: U9.3 (LRCK); also elsewhere on the board
/AF_DAC_MCLK: U9.4 (MCLK); also elsewhere on the board
/AF_DAC_SCLK: U9.2 (SCLK); also elsewhere on the board
GND: C57.2, C60.2, C61.2, C62.2, C63.2, C64.2, C65.2, C67.2, C68.2, C69.1, C106.2, R53.2, R89.2, R90.2, U9.6 (GND), U10.10 (PGND), U10.15 (SGND), U10.17 (EPAD), e4.1 (A); also elsewhere on the board
unnamed: C58.2, R49.1, R89.1
unnamed: C59.2, R50.1, R90.1
unnamed: C59.1, U9.8 (AOUTL)
unnamed: C58.1, U9.5 (AOUTR)
unnamed: C57.1, C60.1, FB7.1, U9.7 (VDD)
unnamed: C66.1, U10.11 (CAP+)
unnamed: C66.2, U10.9 (CAP-)
unnamed: C68.1, U10.12 (HPVDD)
unnamed: C65.1, U10.8 (HPVSS)
unnamed: C61.1, R49.2, U10.2 (INL+)
unnamed: C63.1, U10.1 (INL-)
unnamed: C62.1, R50.2, U10.3 (INR+)
unnamed: C64.1, U10.4 (INR-)
unnamed: J9.T, TP7.1 (1_1), U10.16 (OUTL)
unnamed: J9.R, TP8.1 (1_1), U10.5 (OUTR)
unnamed: C69.2, J9.S, R53.1, e4.2 (B)
VDDA: JP6.2 (B); also elsewhere on the board
